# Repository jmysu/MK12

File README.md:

# MK12

An Arduino MKR w/ ESP-12F WiFi vaporware!

 <br>

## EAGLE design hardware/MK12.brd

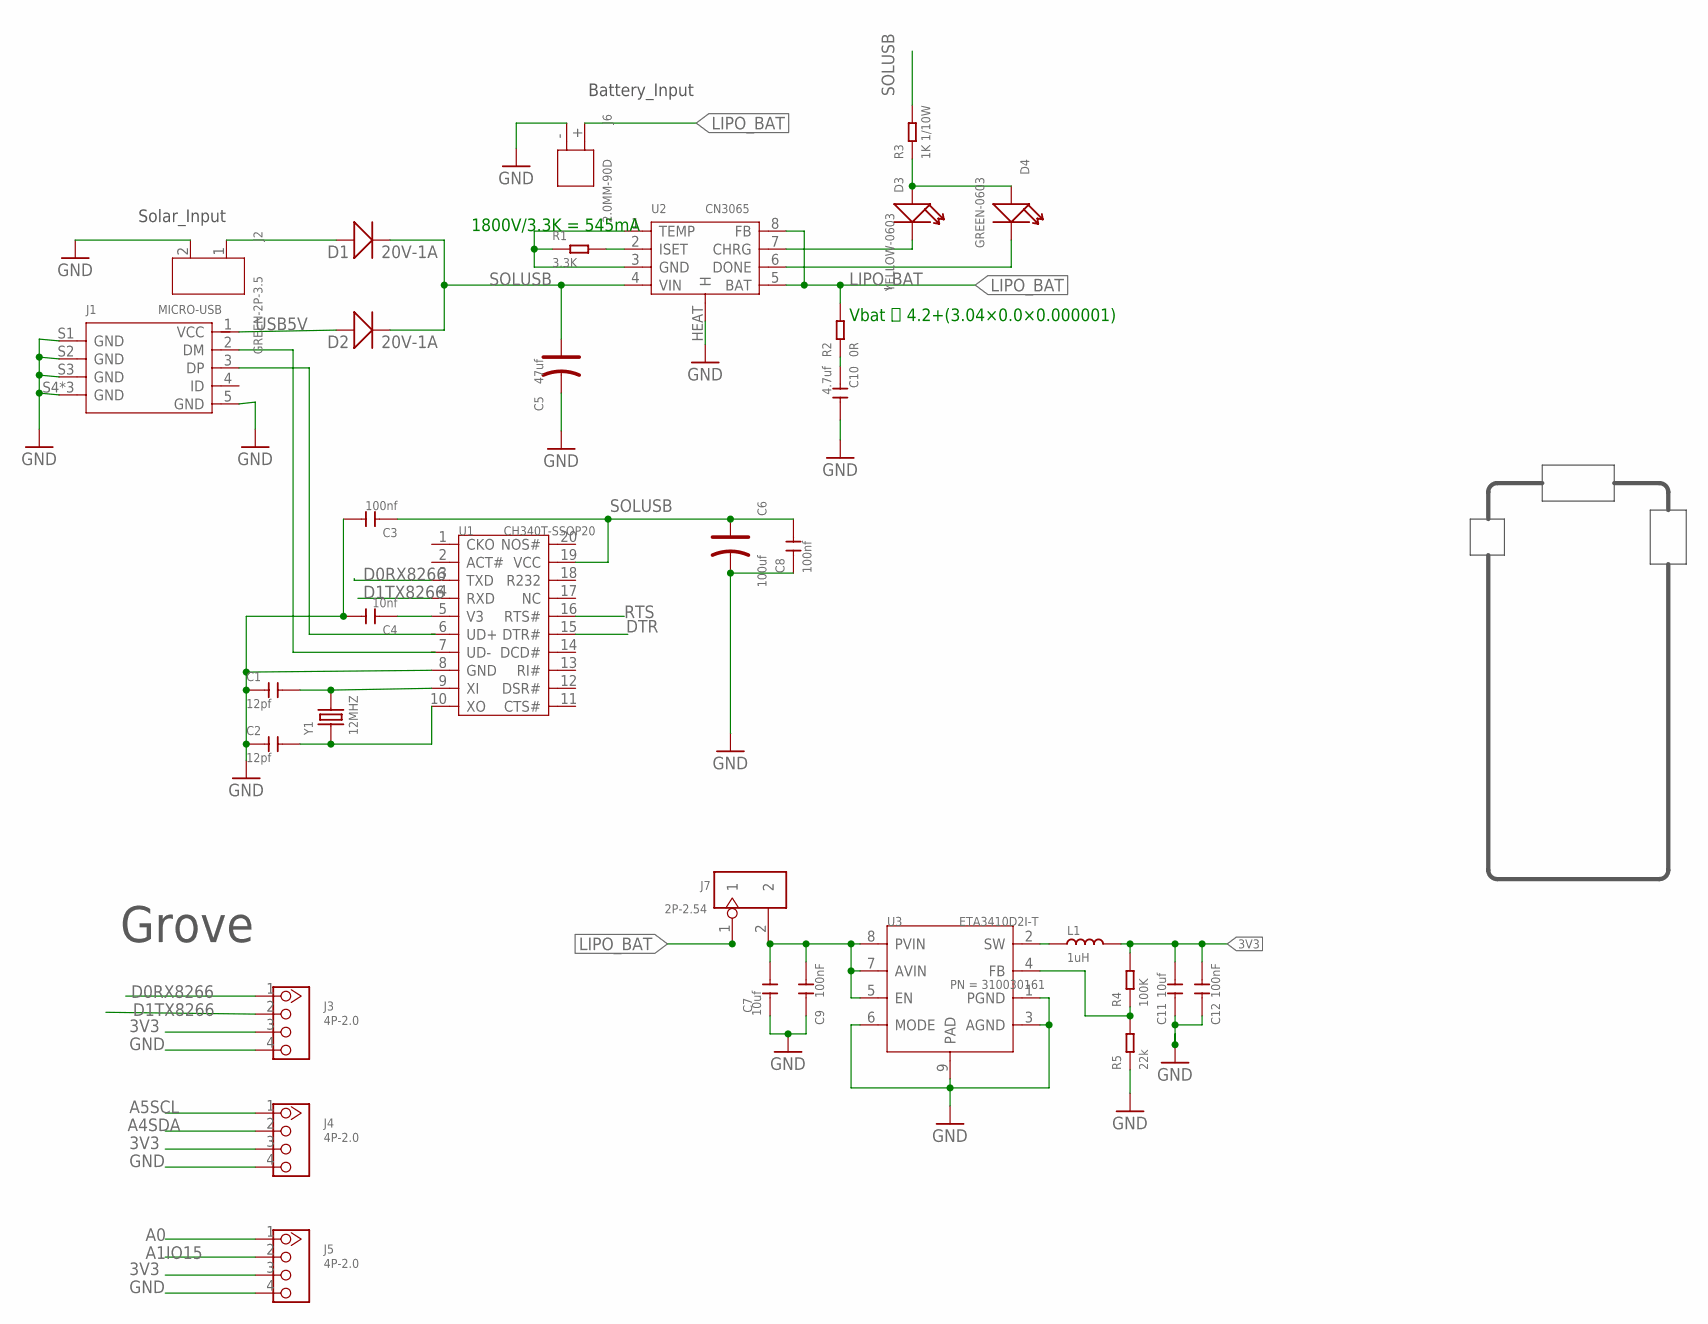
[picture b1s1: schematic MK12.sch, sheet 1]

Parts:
C1, C2: 12pf; C0402
C3, C8: 100nf; C0603
C4: 10nf; C0603
C5: 47uf; AVX-A
C6: 100uf; AVX-B
C7, C11: 10uf; C0805
C9, C12: 100nF; C0402
C10: 4.7uf; C0603
D1, D2: 20V-1A; SOD-123
D3: YELLOW-0603; LED-0603
D4: GREEN-0603; LED-0603
J1: MICRO-USB; MICRO-USB5+4P-SMD-0.65-B
J2: GREEN-2P-3.5; H2-3.5-7.0X7.0MM
J3, J4, J5: 4P-2.0; HW4-2.0
J6: 2.0MM-90D; H2-2.0-90D
J7: 2P-2.54; H2-2.54
L1: 1uH; L0603
R1: 3.3K; R0603
R2: 0R; R0603
R3: 1K 1/10W; R0603
R4: 100K; R0402
R5: 22k; R0402
U1: CH340T-SSOP20; SSOP20-0.65-7.6X5.2MM
U2: CN3065; DFN-8
U3: ETA3410D2I-T; DFN8G-0.5-2X2MM
Y1: 12MHZ; X2-SMD-5.0X3.2X1.3MM

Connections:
3V3: C11.2, C12.2, J3.3, J4.3, J5.3, L1.2, R4.2; also elsewhere on the board
A0: J5.1; also elsewhere on the board
A1IO15: J5.2; also elsewhere on the board
A4SDA: J4.2; also elsewhere on the board
A5SCL: J4.1; also elsewhere on the board
BAT_3V3_IN: C7.2, C9.2, J7.2, U3.5 (EN), U3.7 (AVIN), U3.8 (PVIN)
D0RX8266: J3.1, U1.3 (TXD); also elsewhere on the board
D1TX8266: J3.2, U1.4 (RXD); also elsewhere on the board
DTR: U1.15 (DTR#); also elsewhere on the board
GND: C1.1, C2.1, C3.2, C4.2, C5.-, C6.-, C7.1, C8.1, C9.1, C10.2, C11.1, C12.1, J1.5 (GND), J1.S1 (GND), J1.S2 (GND), J1.S3 (GND), J1.S4 (GND), J1.S5 (GND), J1.S6 (GND), J2.2, J3.4, J4.4, J5.4, J6.-, R1.1, R5.1, U1.8 (GND), U2.1 (TEMP), U2.3 (GND), U2.HEAT (H), U3.1 (PGND), U3.3 (AGND), U3.6 (MODE), U3.9 (PAD); also elsewhere on the board
LIPO_BAT: J6.+, J7.1, R2.2, U2.5 (BAT), U2.8 (FB)
unnamed: D3.+, D4.+, R3.1
unnamed: L1.1, U3.2 (SW)
unnamed: R4.1, R5.2, U3.4 (FB)
unnamed: C1.2, U1.9 (XI), Y1.2
unnamed: C2.2, U1.10 (XO), Y1.1
unnamed: R1.2, U2.2 (ISET)
unnamed: D3.-, U2.7 (CHRG)
unnamed: J1.2 (DM), U1.7 (UD-)
unnamed: C10.1, R2.1
unnamed: J1.3 (DP), U1.6 (UD+)
unnamed: D4.-, U2.6 (DONE)
RTS: U1.16 (RTS#); also elsewhere on the board
SOLAR: D1.+, J2.1
SOLUSB: C3.1, C5.+, C6.+, C8.2, D1.-, D2.-, R3.2, U1.19 (VCC), U2.4 (VIN)
USB5V: D2.+, J1.1 (VCC)
V3: C4.1, U1.5 (V3)

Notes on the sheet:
Solar_Input
Battery_Input
Vbat ＝ 4.2+(3.04×0.0×0.000001)
1800V/3.3K = 545mA
Grove

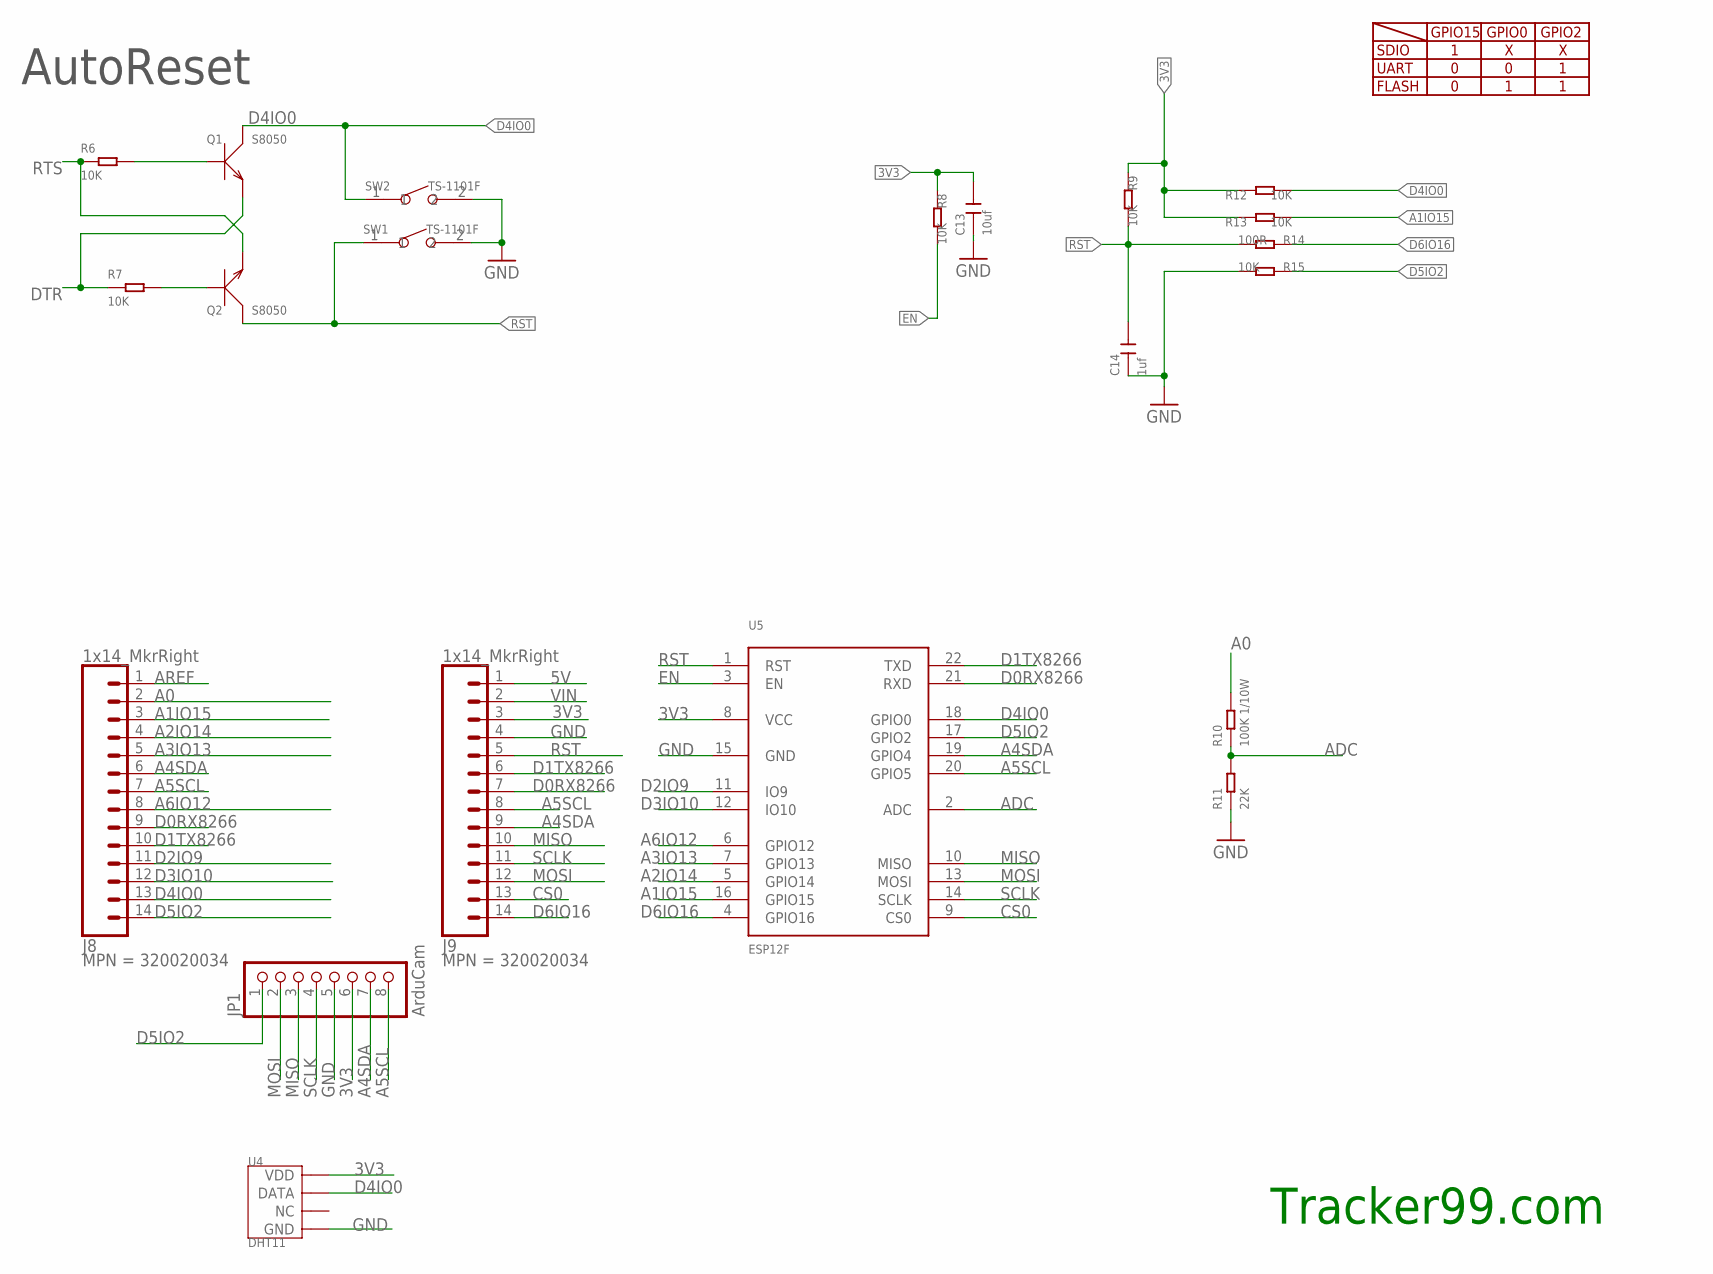
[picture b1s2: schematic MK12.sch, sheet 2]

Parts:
C13: 10uf; C0603
C14: 1uf; C0603
J8, J9: 1x14_MkrRight; 1X14_LOCK; MPN 320020034
JP1: ArduCam; MILLER_1X08-LOCK
Q1, Q2: S8050; SOT-23
R6, R7: 10K; R0402
R8, R9, R12, R13, R15: 10K; SEEED-RESISTOR_R0402
R10: 100K 1/10W; R0603
R11: 22K; R0603
R14: 100R; R0603
SW1, SW2: TS-1101F; SW2-5.0-6.0X3.0X4.3MM
U4: DHT11; SNR4-2.54-15.5X12.0X5.5MM
U5: ESP12F; ESP-12F

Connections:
3V3: C13.2, J9.3, JP1.6, R8.1, R9.1, R12.1, R13.1, U4.1 (VDD), U5.8 (VCC); also elsewhere on the board
5V: J9.1
A0: J8.2, R10.2; also elsewhere on the board
A1IO15: J8.3, R13.2, U5.16 (GPIO15); also elsewhere on the board
A2IO14: J8.4, U5.5 (GPIO14)
A3IO13: J8.5, U5.7 (GPIO13)
A4SDA: J8.6, J9.9, JP1.7, U5.19 (GPIO4); also elsewhere on the board
A5SCL: J8.7, J9.8, JP1.8, U5.20 (GPIO5); also elsewhere on the board
A6IO12: J8.8, U5.6 (GPIO12)
ADC: R10.1, R11.2, U5.2 (ADC)
AREF: J8.1
CS0: J9.13, U5.9 (CS0)
D0RX8266: J8.9, J9.7, U5.21 (RXD); also elsewhere on the board
D1TX8266: J8.10, J9.6, U5.22 (TXD); also elsewhere on the board
D2IO9: J8.11, U5.11 (IO9)
D3IO10: J8.12, U5.12 (IO10)
D4IO0: J8.13, Q1.3 (C), R12.2, SW2.1, U4.2 (DATA), U5.18 (GPIO0)
D5IO2: J8.14, JP1.1, R15.1, U5.17 (GPIO2)
D6IO16: J9.14, R14.1, U5.4 (GPIO16)
DTR: Q1.2 (E), R7.1; also elsewhere on the board
EN: R8.2, U5.3 (EN)
GND: C13.1, C14.1, J9.4, JP1.5, R11.1, R15.2, SW1.2, SW2.2, U4.4 (GND), U5.15 (GND); also elsewhere on the board
MISO: J9.10, JP1.3, U5.10 (MISO)
MOSI: J9.12, JP1.2, U5.13 (MOSI)
unnamed: Q2.1 (B), R7.2
unnamed: Q1.1 (B), R6.2
RST: C14.2, J9.5, Q2.3 (C), R9.2, R14.2, SW1.1, U5.1 (RST)
RTS: Q2.2 (E), R6.1; also elsewhere on the board
SCLK: J9.11, JP1.4, U5.14 (SCLK)
VIN: J9.2

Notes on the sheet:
SDIO
UART
FLASH
GPIO15
GPIO0
GPIO2
Tracker99.com
AutoReset

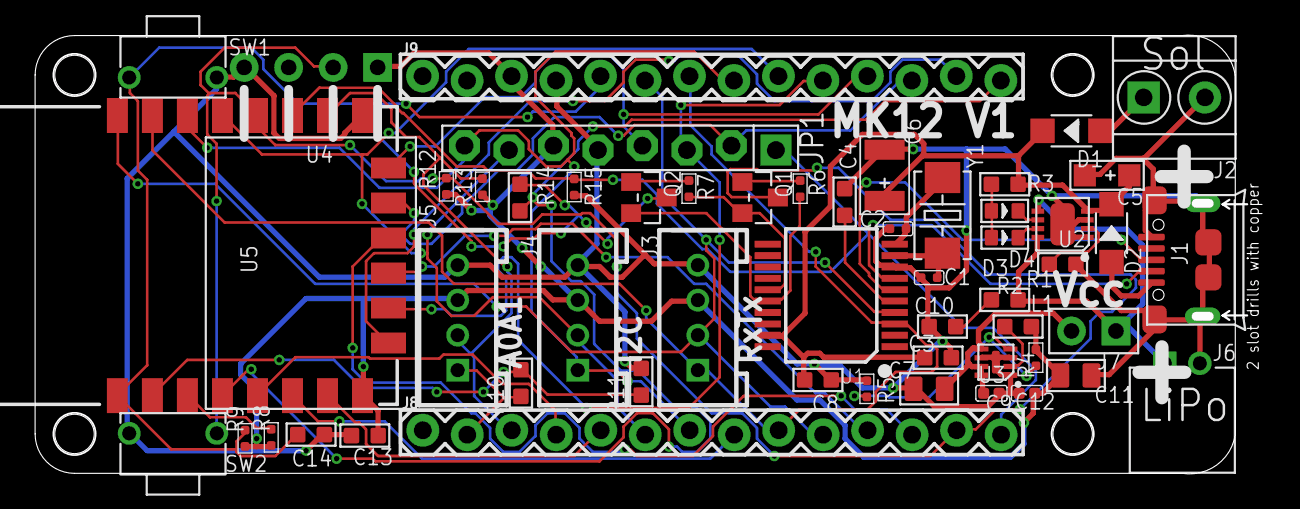
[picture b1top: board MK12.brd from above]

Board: 2 copper layers, 69.7 x 24.6 mm, 58 parts (0 on the bottom side), 44 nets.

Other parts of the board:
U$5, U$6, U$7, U$8: MH_RND_F_2.2MM_NM

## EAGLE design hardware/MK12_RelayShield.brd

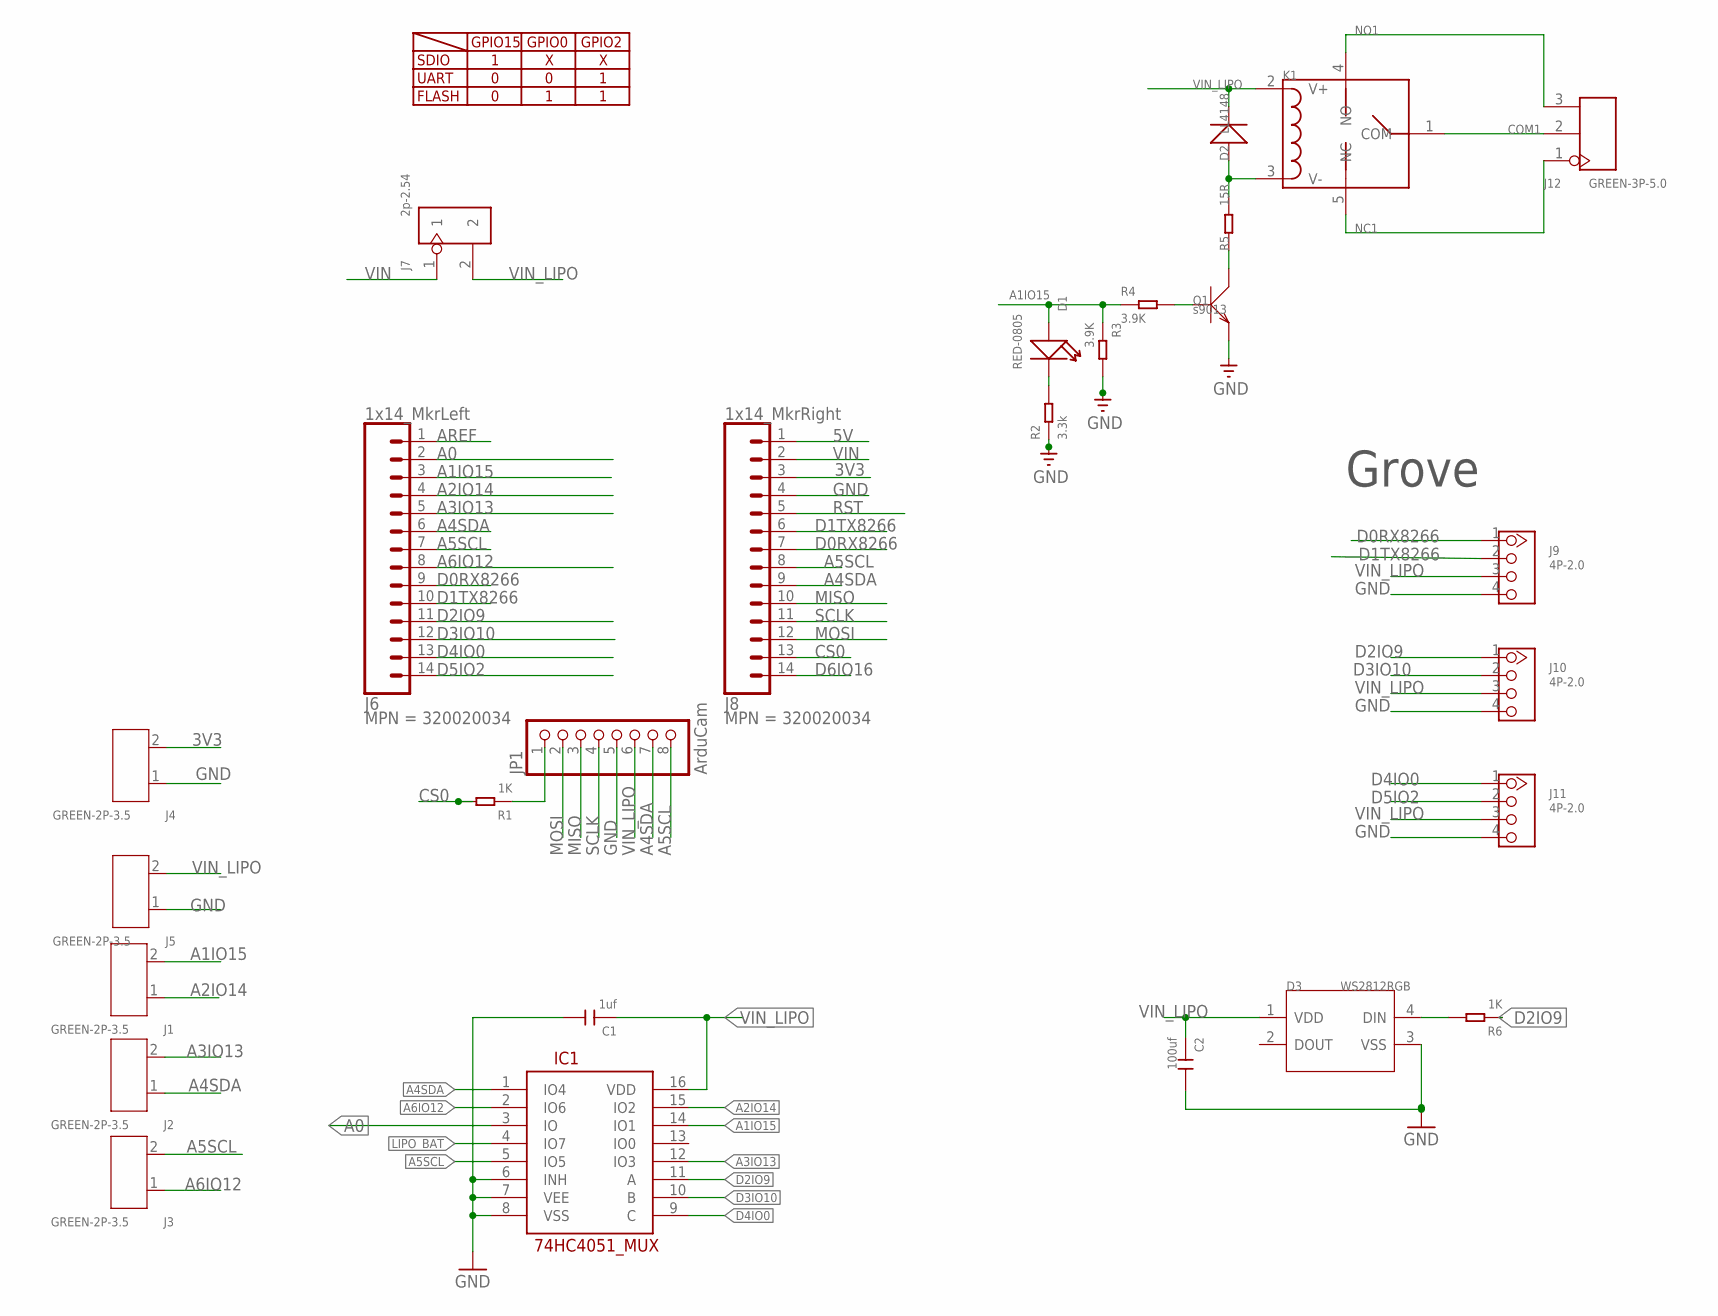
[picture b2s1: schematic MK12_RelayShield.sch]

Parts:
C1: 1uf; C0603
C2: 100uf; C1206
D1: RED-0805; LED-0805
D2: LL4148; LL-34
D3: WS2812RGB; LED4-SMD-5050
IC1: 74HC4051_MUX; SPARKFUN_SO16
J1, J2, J3, J4, J5: GREEN-2P-3.5; H2-3.5-7.0X7.0MM
J6: 1x14_MkrLeft; 1X14_LOCK; MPN 320020034
J7: 2p-2.54; H2-2.54
J8: 1x14_MkrRight; 1X14_LOCK; MPN 320020034
J9, J10, J11: 4P-2.0; HW4-2.0
J12: GREEN-3P-5.0; H3-5.0-15.5X8.0MM
JP1: ArduCam; MILLER_1X08-LOCK
K1: RELAY-HLS8L-DC5V-S-CHLS8L-DC5V-S-C; REY5-19.0X15.0X15.0MM
Q1: s9013; SOT23
R1, R6: 1K; R0805
R2: 3.3k; R0603
R3, R4: 3.9K; R0603
R5: 15R; R0603

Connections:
3V3: J4.2, J8.3
5V: J8.1
A0: IC1.3 (IO), J6.2
A1IO15: D1.+, IC1.14 (IO1), J1.2, J6.3, R3.1, R4.1
A2IO14: IC1.15 (IO2), J1.1, J6.4
A3IO13: IC1.12 (IO3), J2.2, J6.5
A4SDA: IC1.1 (IO4), J2.1, J6.6, J8.9, JP1.7
A5SCL: IC1.5 (IO5), J3.2, J6.7, J8.8, JP1.8
A6IO12: IC1.2 (IO6), J3.1, J6.8
AREF: J6.1
COM1: J12.2, K1.1 (COM)
CS0: J8.13, R1.2
D0RX8266: J6.9, J8.7, J9.1
D1TX8266: J6.10, J8.6, J9.2
D2IO9: IC1.11 (A), J6.11, J10.1, R6.1
D3IO10: IC1.10 (B), J6.12, J10.2
D4IO0: IC1.9 (C), J6.13, J11.1
D5IO2: J6.14, J11.2
D6IO16: J8.14
GND: C1.2, C2.2, D3.3 (VSS), IC1.6 (INH), IC1.7 (VEE), IC1.8 (VSS), J4.1, J5.1, J8.4, J9.4, J10.4, J11.4, JP1.5, Q1.2 (E), R2.1, R3.2
LIPO_BAT: IC1.4 (IO7)
MISO: J8.10, JP1.3
MOSI: J8.12, JP1.2
unnamed: Q1.1 (B), R4.2
unnamed: D2.A (+), K1.3 (V-), R5.2
unnamed: Q1.3 (C), R5.1
unnamed: D1.-, R2.2
unnamed: D3.4 (DIN), R6.2
unnamed: JP1.1, R1.1
NC1: J12.1, K1.5 (NC)
NO1: J12.3, K1.4 (NO)
RST: J8.5
SCLK: J8.11, JP1.4
VIN: J7.1, J8.2
VIN_LIPO: C1.1, C2.1, D2.C (-), D3.1 (VDD), IC1.16 (VDD), J5.2, J7.2, J9.3, J10.3, J11.3, JP1.6, K1.2 (V+)

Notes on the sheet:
SDIO
UART
FLASH
GPIO15
GPIO0
GPIO2
Grove

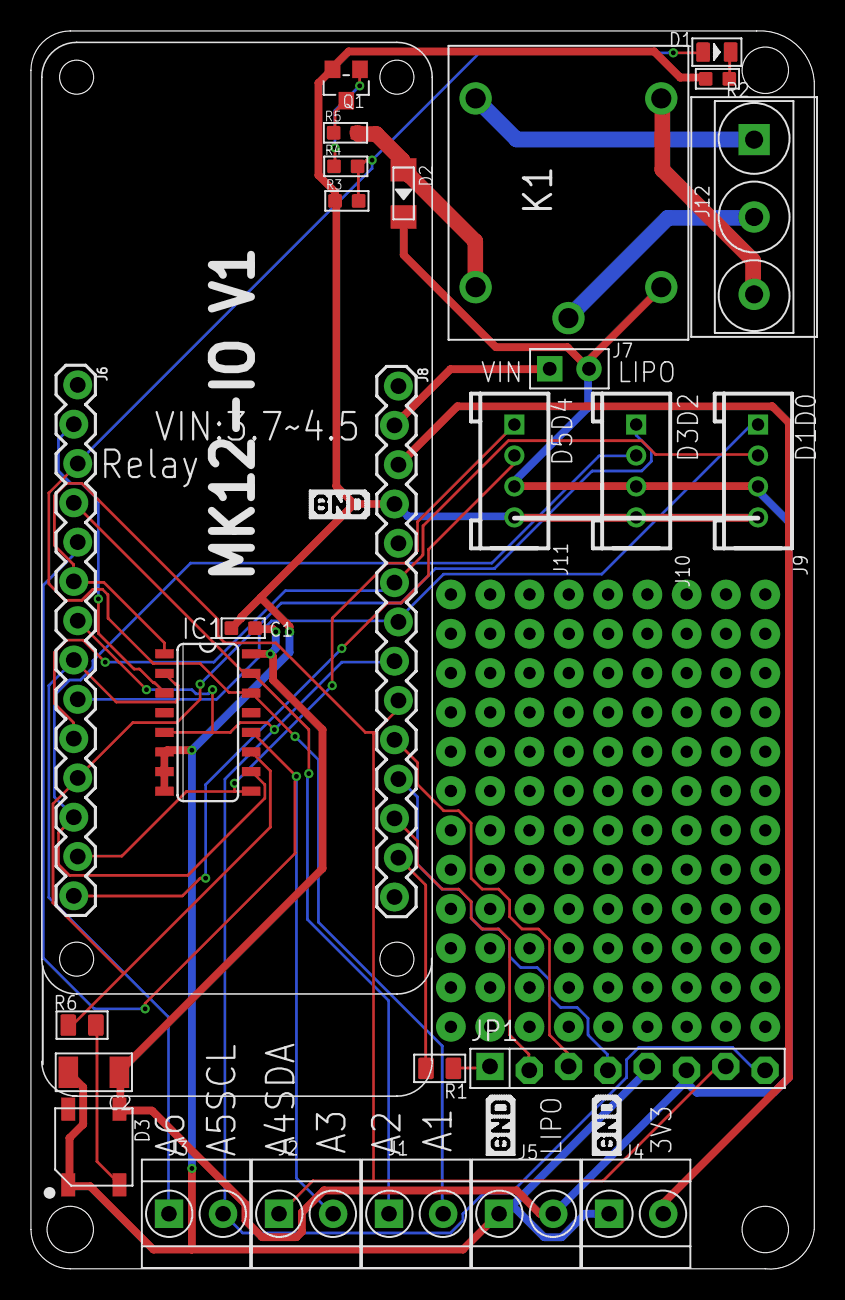
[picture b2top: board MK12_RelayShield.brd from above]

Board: 2 copper layers, 50.6 x 80.0 mm, 27 parts (0 on the bottom side), 30 nets.

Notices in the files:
parts and their libraries:
SparkFun-Connectors: Licensing: Creative Commons ShareAlike 4.0 International - https://creativecommons.org/licenses/by-sa/4.0
